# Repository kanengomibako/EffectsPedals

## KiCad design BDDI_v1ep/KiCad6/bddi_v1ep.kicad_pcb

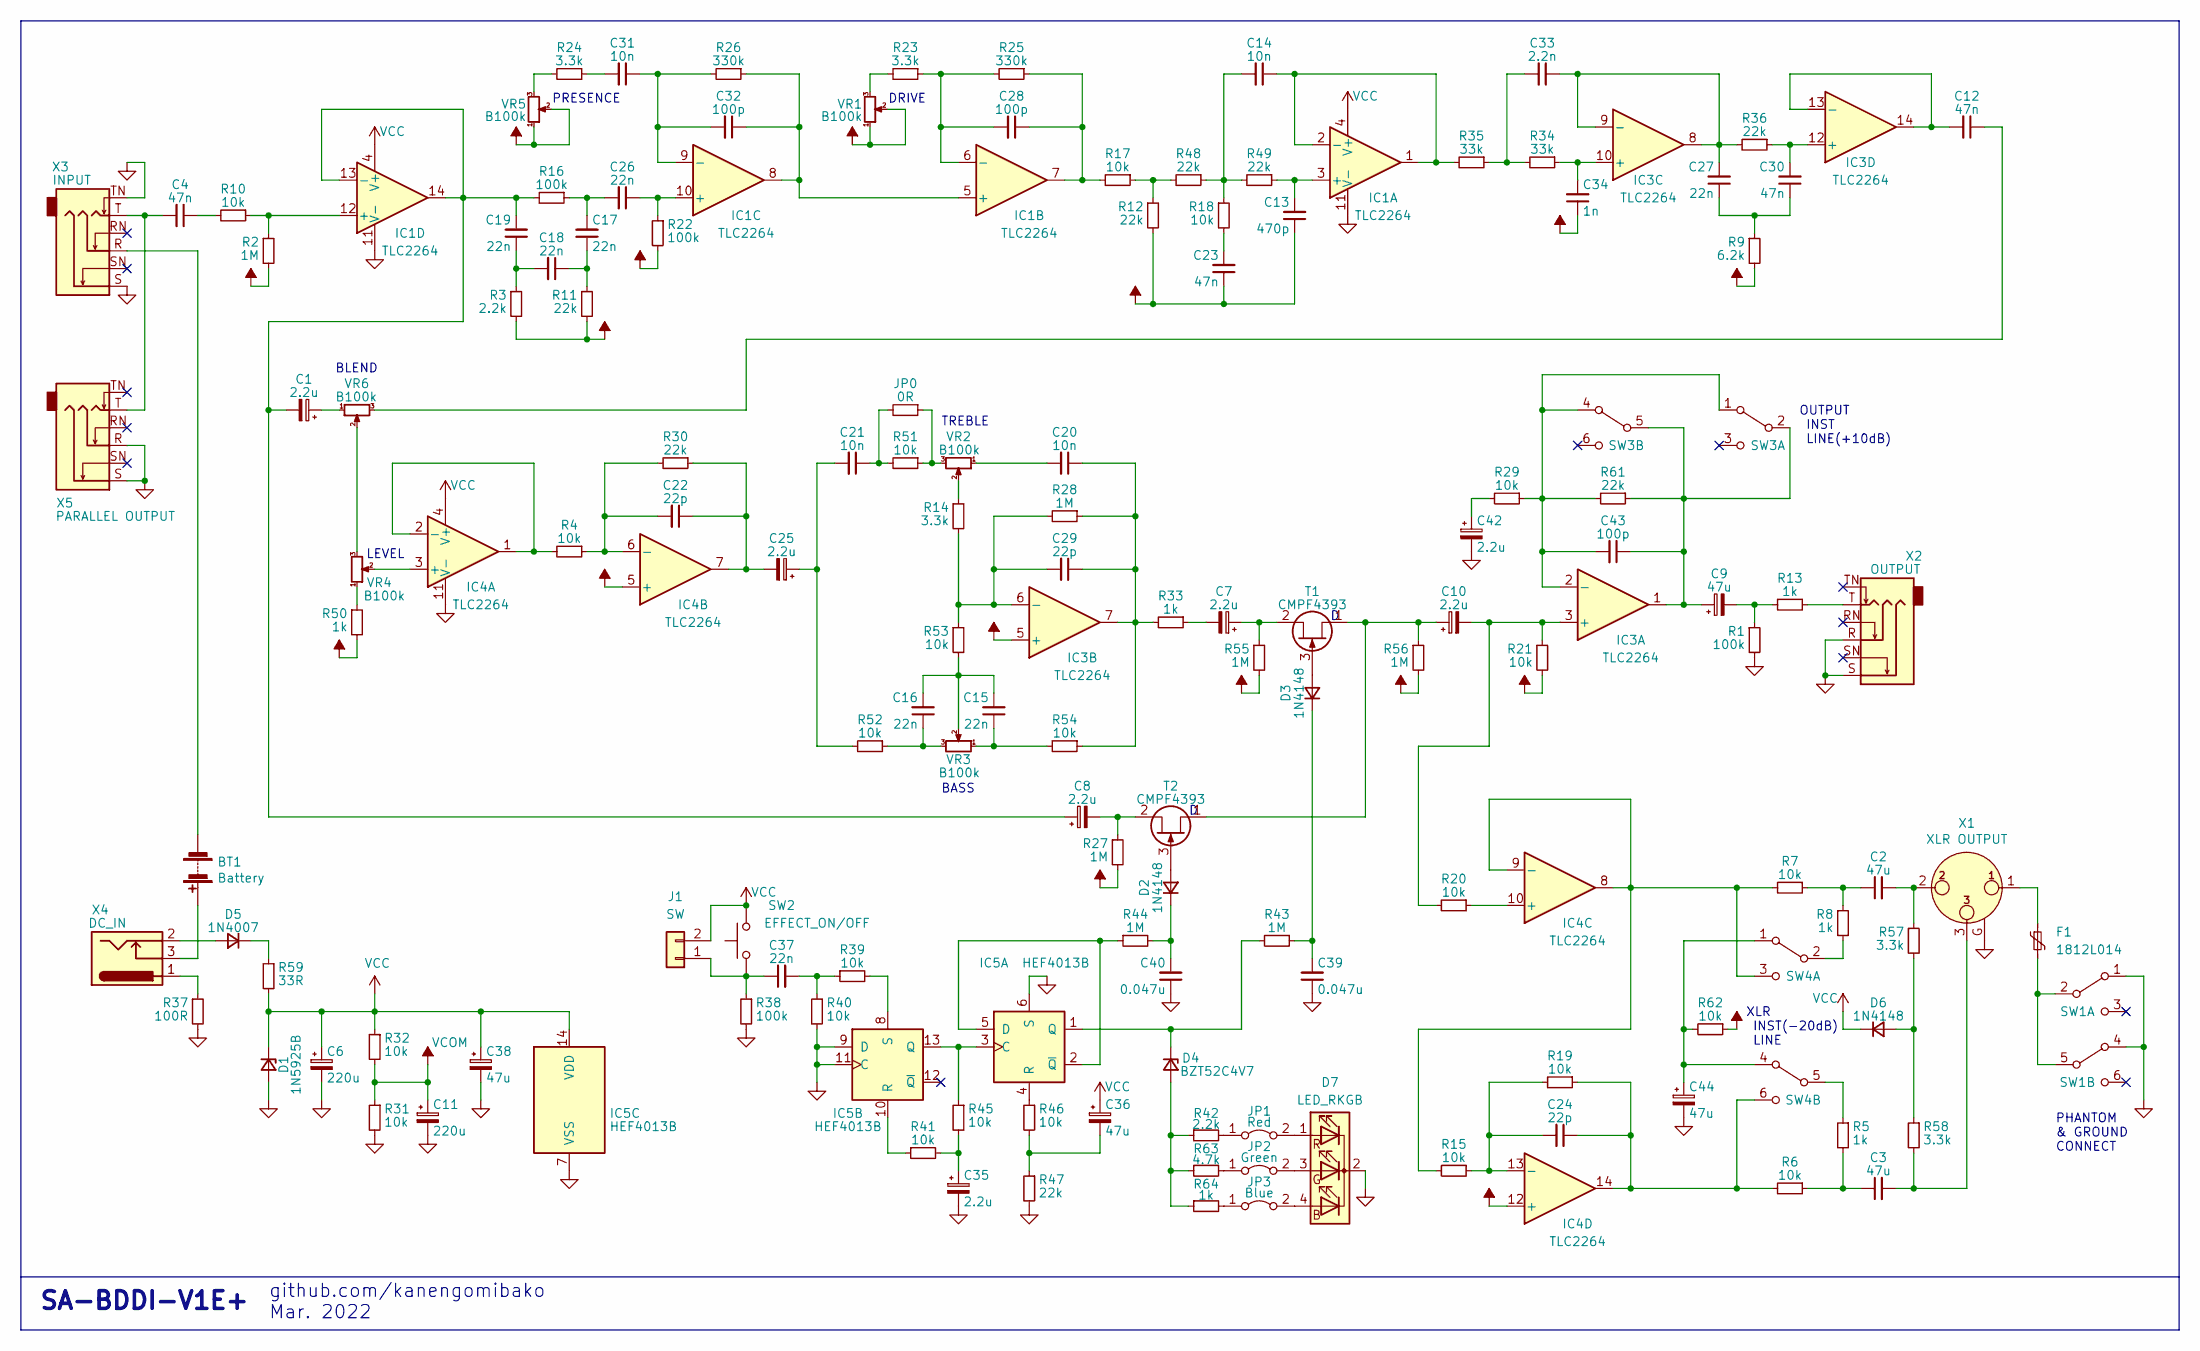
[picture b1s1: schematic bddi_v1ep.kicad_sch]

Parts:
BT1: Battery; PinHeader_1x02_P2.54mm_Vertical
C1, C7, C8, C10, C25, C35, C42: 2.2u; CP_Radial_D5.0mm_P2.00mm
C2, C3: 47u; CP_Radial_D8.0mm_P2.50mm
C4, C12, C23, C30: 47n; C_1210_3225Metric
C6, C11: 220u; CP_Radial_D6.3mm_P2.50mm
C9, C36, C38, C44: 47u; CP_Radial_D5.0mm_P2.00mm
C13: 470p; C_0603_1608Metric_Pad1.08x0.95mm_HandSolder
C14, C20, C21, C31: 10n; C_0603_1608Metric_Pad1.08x0.95mm_HandSolder
C15, C16, C17, C18, C19, C26, C27, C37: 22n; C_0805_2012Metric
C22, C24, C29: 22p; C_0603_1608Metric_Pad1.08x0.95mm_HandSolder
C28, C32, C43: 100p; C_0603_1608Metric_Pad1.08x0.95mm_HandSolder
C33: 2.2n; C_0603_1608Metric_Pad1.08x0.95mm_HandSolder
C34: 1n; C_0603_1608Metric_Pad1.08x0.95mm_HandSolder
C39, C40: 0.047u; C_0603_1608Metric_Pad1.08x0.95mm_HandSolder
D1: 1N5925B; D_DO-41_SOD81_P7.62mm_Horizontal
D2, D3, D6: 1N4148; my_D_GS1010FL
D4: BZT52C4V7; my_D_GS1010FL
D5: 1N4007; D_DO-41_SOD81_P7.62mm_Horizontal
D7: LED_RKGB; LED_D5.0mm-4_RGB
F1: 1812L014; R_1812_4532Metric
IC1, IC3, IC4: TLC2264; TSSOP-14_4.4x5mm_P0.65mm
IC5: HEF4013B; SOIC-14_3.9x8.7mm_P1.27mm
J1: SW; PinHeader_1x02_P2.54mm_Vertical
JP0: 0R; my_SolderJumper-THpad
JP1: Red; my_SolderJumper-THpad
JP2: Green; my_SolderJumper-THpad
JP3: Blue; my_SolderJumper-THpad
R1, R16, R22, R38: 100k; R_0603_1608Metric_Pad0.98x0.95mm_HandSolder
R2, R27, R28, R43, R44, R55, R56: 1M; R_0603_1608Metric_Pad0.98x0.95mm_HandSolder
R3, R42: 2.2k; R_0603_1608Metric_Pad0.98x0.95mm_HandSolder
R4, R6, R7, R10, R15, R17, R18, R19, R20, R21, R29, R31, R32, R39, R40, R41, R45, R46, R51, R52, R53, R54, R62: 10k; R_0603_1608Metric_Pad0.98x0.95mm_HandSolder
R5, R8, R13, R33, R50, R64: 1k; R_0805_2012Metric
R9: 6.2k; R_0603_1608Metric_Pad0.98x0.95mm_HandSolder
R11, R12, R30, R36, R47, R48, R49, R61: 22k; R_0603_1608Metric_Pad0.98x0.95mm_HandSolder
R14, R23, R24, R57, R58: 3.3k; R_0603_1608Metric_Pad0.98x0.95mm_HandSolder
R25, R26: 330k; R_0603_1608Metric_Pad0.98x0.95mm_HandSolder
R34, R35: 33k; R_0603_1608Metric_Pad0.98x0.95mm_HandSolder
R37: 100R; R_Axial_DIN0309_L9.0mm_D3.2mm_P12.70mm_Horizontal
R59: 33R; R_Axial_DIN0516_L15.5mm_D5.0mm_P20.32mm_Horizontal
R63: 4.7k; R_0603_1608Metric_Pad0.98x0.95mm_HandSolder
SW1, SW3, SW4: sw; PinHeader_2x03_P2.54mm_Vertical
SW2: EFFECT_ON/OFF; SW_Cherry_MX_1.00u_PCB
T1, T2: CMPF4393; SOT-23
VR1, VR2, VR3, VR4, VR5, VR6: B100k; my_pot_5mm_widePad
X1: XLR OUTPUT; PinHeader_1x04_P2.54mm_Vertical
X2: OUTPUT; my_Phone_Jack_Daier
X3: INPUT; my_Phone_Jack_Daier
X4: DC_IN; my_DC_Jack
X5: PARALLEL OUTPUT; my_Phone_Jack_Daier

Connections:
GND: C6.2, C11.2, C35.2, C38.2, C39.1, C40.1, C42.2, C44.2, D1.2 (A), D7.2 (K), IC1.11 (V-), IC3.11 (V-), IC4.11 (V-), IC5.6 (S), IC5.7 (VSS), IC5.9 (D), IC5.11 (C), R1.2, R31.2, R37.2, R38.2, R40.2, R47.2, SW1.1 (A), SW1.4 (A), X1.G, X2.R, X2.S, X3.S, X3.TN, X5.R, X5.S
unnamed: BT1.1 (+), X4.3
unnamed: BT1.2 (-), X3.R
unnamed: C1.1, VR6.1
unnamed: C1.2, C8.1, C19.2, IC1.13 (-), IC1.14, R16.2
unnamed: C2.1, R7.1, R8.1
unnamed: C2.2, R57.1, X1.2
unnamed: C3.1, R5.2, R6.1
unnamed: C3.2, R58.2, X1.3
unnamed: C4.1, R10.2
unnamed: C4.2, X3.T, X5.T
unnamed: C7.1, R55.1, T1.2 (S)
unnamed: C7.2, R33.1
unnamed: C8.2, R27.1, T2.2 (S)
unnamed: C9.2, R1.1, R13.2
unnamed: C10.1, R56.1, T1.1 (D), T2.1 (D)
unnamed: C10.2, IC3.3 (+), R20.2, R21.1
unnamed: C12.1, VR6.3
unnamed: C12.2, IC3.13 (-), IC3.14
unnamed: C13.2, IC1.3 (+), R49.1
unnamed: C14.1, IC1.1, IC1.2 (-), R35.2
unnamed: C14.2, R18.1, R48.1, R49.2
unnamed: C15.1, R54.2, VR3.1
unnamed: C15.2, C16.2, R53.2, VR3.2
unnamed: C16.1, R52.1, VR3.3
unnamed: C17.1, C18.1, R11.1
unnamed: C17.2, C26.2, R16.1
unnamed: C18.2, C19.1, R3.1
unnamed: C20.1, C29.1, IC3.7, R28.1, R33.2, R54.1
unnamed: C20.2, VR2.1
unnamed: C21.1, JP0.2, R51.2
unnamed: C21.2, C25.1, R52.2
unnamed: C22.1, C25.2, IC4.7, R30.1
unnamed: C22.2, IC4.6 (-), R4.1, R30.2
unnamed: C23.2, R18.2
unnamed: C24.1, IC4.14, R6.2, R19.1, SW4.6 (C)
unnamed: C24.2, IC4.13 (-), R15.1, R19.2
unnamed: C26.1, IC1.10 (+), R22.1
unnamed: C27.1, C30.1, R9.1
unnamed: C27.2, C33.1, IC3.8, IC3.9 (-), R36.2
unnamed: C28.1, IC1.7, R17.2, R25.1
unnamed: C28.2, IC1.6 (-), R23.1, R25.2
unnamed: C29.2, IC3.6 (-), R14.2, R28.2, R53.1
unnamed: C30.2, IC3.12 (+), R36.1
unnamed: C31.1, C32.2, IC1.9 (-), R26.2
unnamed: C31.2, R24.1
unnamed: C32.1, IC1.5 (+), IC1.8, R26.1
unnamed: C33.2, R34.2, R35.1
unnamed: C34.2, IC3.10 (+), R34.1
unnamed: C35.1, R41.2, R45.2
unnamed: C36.2, R46.2, R47.1
unnamed: C37.1, J1.1, R38.1, SW2.2
unnamed: C37.2, R39.1, R40.1
unnamed: C39.2, D3.1 (K), R43.1
unnamed: C40.2, D2.1 (K), R44.2
unnamed: C42.1, R29.2
unnamed: C9.1, C43.1, IC3.1, R61.1, SW3.2 (B), SW3.5 (B)
unnamed: C43.2, IC3.2 (-), R29.1, R61.2, SW3.1 (A), SW3.4 (A)
unnamed: C44.1, R62.2, SW4.1 (A), SW4.4 (A)
unnamed: D2.2 (A), T2.3 (G)
unnamed: D3.2 (A), T1.3 (G)
unnamed: D4.1 (K), IC5.1 (Q), R43.2
unnamed: D4.2 (A), R42.1, R63.1, R64.1
unnamed: D5.1 (K), R59.1
unnamed: D5.2 (A), X4.2
unnamed: D6.2 (A), R57.2, R58.1
unnamed: D7.1 (RA), JP1.2 (B)
unnamed: D7.3 (GA), JP2.2 (B)
unnamed: D7.4 (BA), JP3.2 (B)
unnamed: F1.1, X1.1
unnamed: F1.2, SW1.2 (B), SW1.5 (B)
unnamed: IC1.12 (+), R2.1, R10.1
unnamed: IC4.1, IC4.2 (-), R4.2
unnamed: IC4.3 (+), VR4.2
unnamed: IC4.8, IC4.9 (-), R7.2, R15.2, SW4.3 (C)
unnamed: IC4.10 (+), R20.1
unnamed: IC5.2 (~Q), IC5.5 (D), R44.1
unnamed: IC5.4 (R), R46.1
unnamed: IC5.8 (S), R39.2
unnamed: IC5.10 (R), R41.1
unnamed: IC5.3 (C), IC5.13 (Q), R45.1
unnamed: JP0.1, R51.1, VR2.3
unnamed: JP1.1 (A), R42.2
unnamed: JP2.1 (A), R63.2
unnamed: JP3.1 (A), R64.2
unnamed: R5.1, SW4.5 (B)
unnamed: R8.2, SW4.2 (B)
unnamed: R12.1, R17.1, R48.2
unnamed: R13.1, X2.T
unnamed: R14.1, VR2.2
unnamed: R23.2, VR1.3
unnamed: R24.2, VR5.3
unnamed: R37.1, X4.1
unnamed: R50.1, VR4.1
unnamed: VR4.3, VR6.2
VCC: C6.1, C36.1, C38.1, D1.1 (K), D6.1 (K), IC1.4 (V+), IC3.4 (V+), IC4.4 (V+), IC5.14 (VDD), J1.2, R32.1, R59.2, SW2.1
VCOM: C11.1, C13.1, C23.1, C34.1, IC3.5 (+), IC4.5 (+), IC4.12 (+), R2.2, R3.2, R9.2, R11.2, R12.2, R21.2, R22.2, R27.2, R31.1, R32.2, R50.2, R55.2, R56.2, R62.1, VR1.1, VR1.2, VR5.1, VR5.2

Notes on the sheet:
github.com/kanengomibako Mar. 2022
PHANTOM & GROUND CONNECT
XLR INST(-20dB) LINE
BLEND
SA-BDDI-V1E+
OUTPUT INST LINE(+10dB)
PRESENCE
DRIVE
LEVEL
BASS
TREBLE

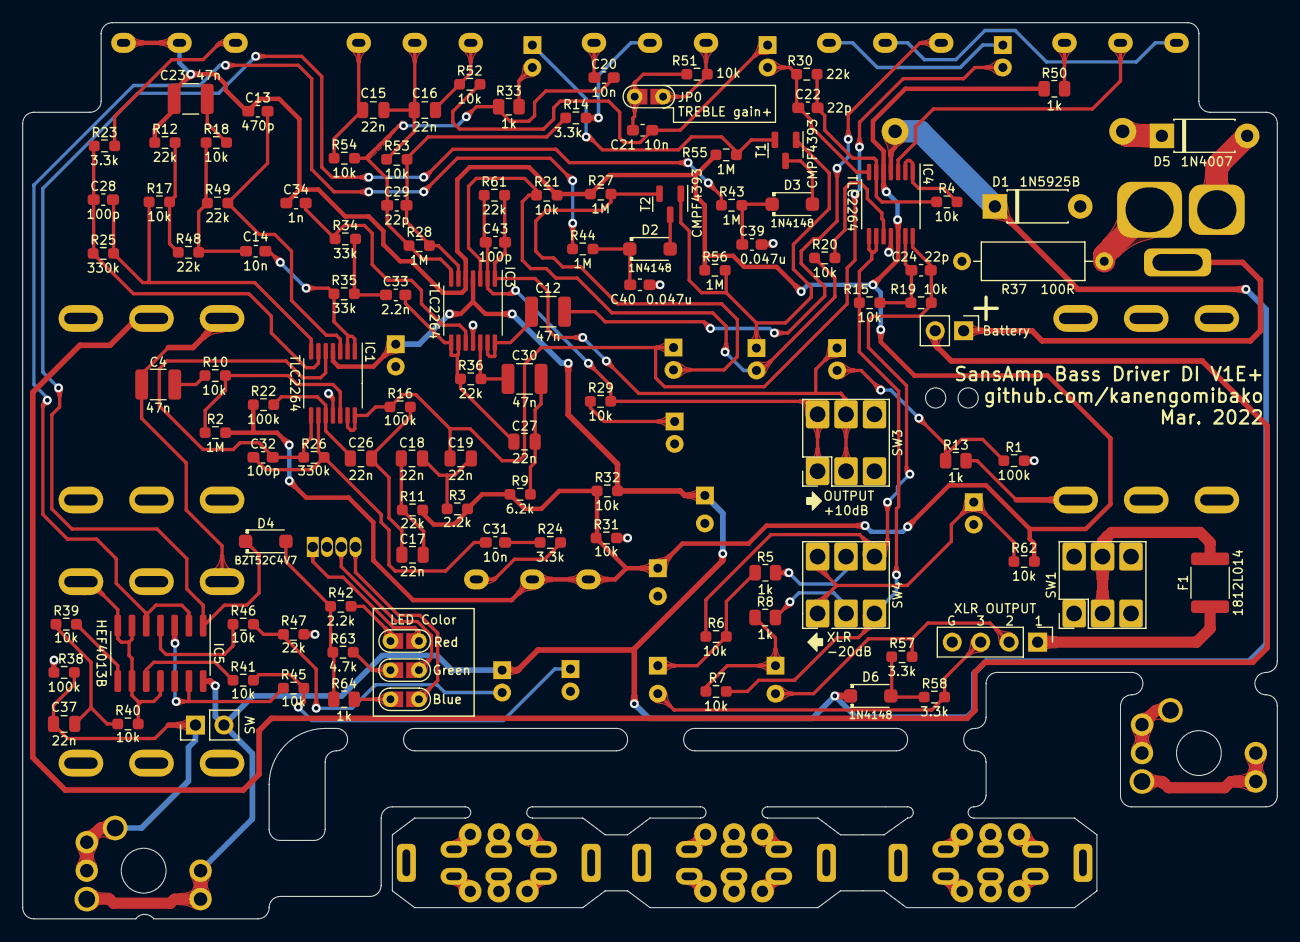
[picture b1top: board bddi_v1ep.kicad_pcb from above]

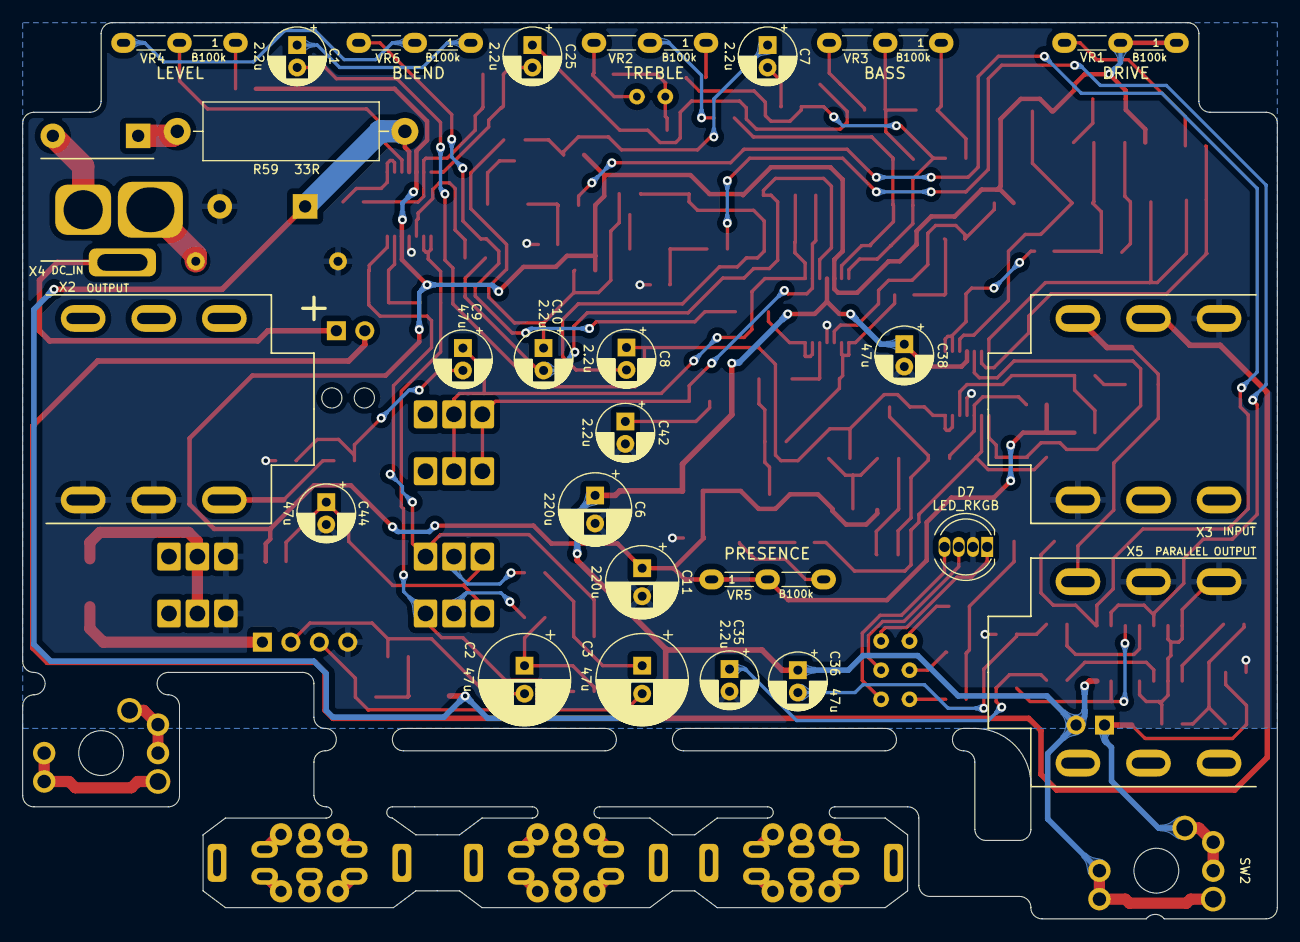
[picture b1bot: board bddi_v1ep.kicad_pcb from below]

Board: 2 copper layers, 112.0 x 80.0 mm, 144 parts (29 on the bottom side), 97 nets.

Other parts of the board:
SW99, SW99#2, SW99#3: sw; PinHeader_2x03_P2.54mm_Vertical
SW99#4: EFFECT_ON/OFF; SW_Cherry_MX_1.00u_PCB

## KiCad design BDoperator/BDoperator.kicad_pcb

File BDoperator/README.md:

BD Operator
[https://kanengomibako.github.io/pages/00362_BDoperator.html](https://kanengomibako.github.io/pages/00362_BDoperator.html)

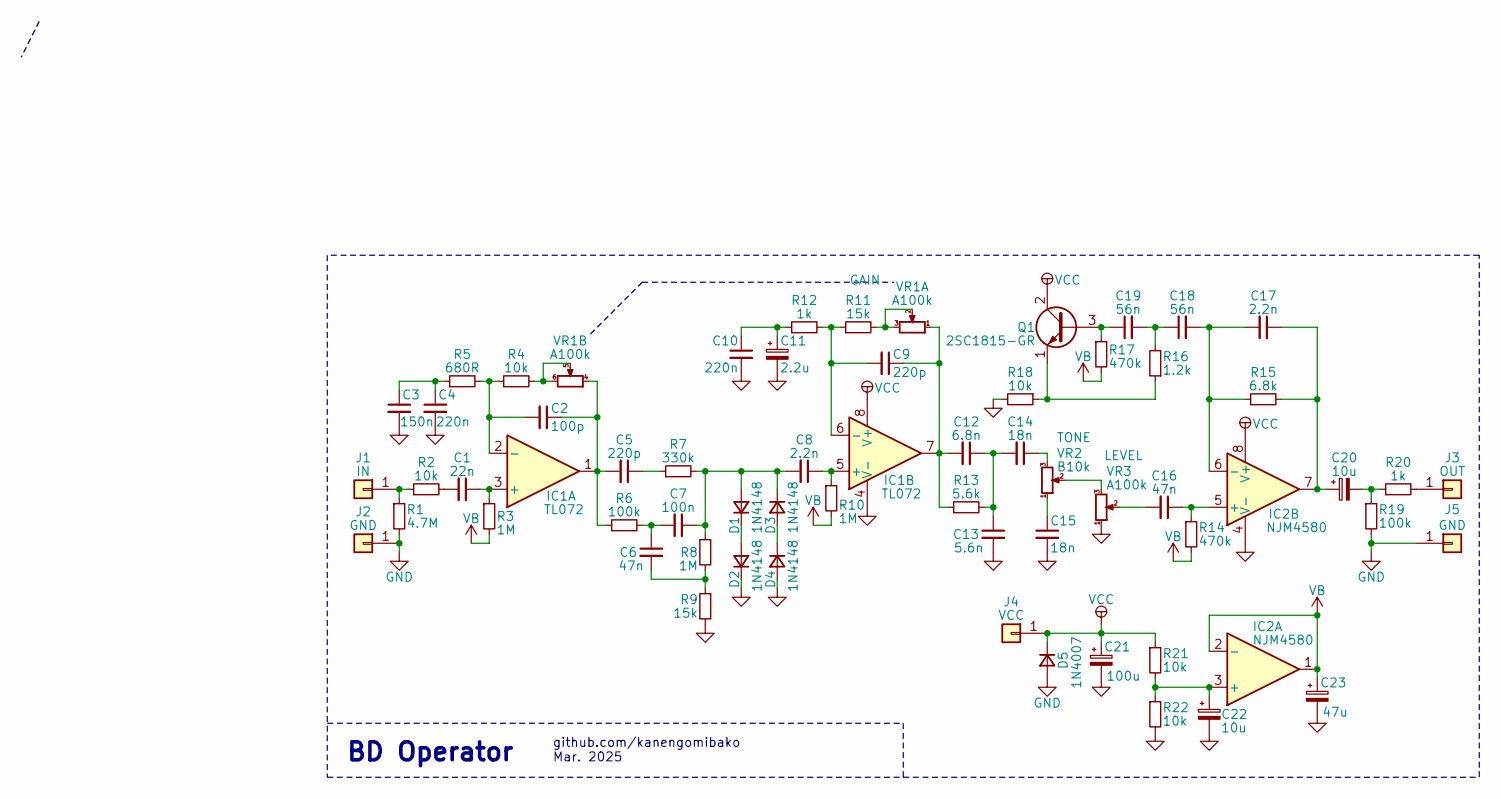
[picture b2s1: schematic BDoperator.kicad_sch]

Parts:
C1: 22n; my_C_Rect1_P5.00mm
C2: 100p; my_C_Rect1_P5.00mm
C3: 150n; my_C_Rect1_P5.00mm
C4, C10: 220n; my_C_Rect1_P5.00mm
C5, C9: 220p; my_C_Rect1_P5.00mm
C6, C16: 47n; my_C_Rect1_P5.00mm
C7: 100n; my_C_Rect1_P5.00mm
C8, C17: 2.2n; my_C_Rect1_P5.00mm
C11: 2.2u; my_C_D5.0mm_P2.50mm
C12: 6.8n; my_C_Rect1_P5.00mm
C13: 5.6n; my_C_Rect1_P5.00mm
C14, C15: 18n; my_C_Rect1_P5.00mm
C18, C19: 56n; my_C_Rect1_P5.00mm
C20, C22: 10u; my_C_D5.0mm_P2.50mm
C21: 100u; my_C_D6.3mm_P2.50mm
C23: 47u; my_C_D5.0mm_P2.50mm
D1, D2, D3, D4: 1N4148; my_D_P7.62mm
D5: 1N4007; my_D_P7.62mm
IC1: TL072; DIP-8_W7.62mm
IC2: NJM4580; DIP-8_W7.62mm
J1: IN; my_WirePad_0-8mmDrill
J2, J5: GND; my_WirePad_0-8mmDrill
J3: OUT; my_WirePad_0-8mmDrill
J4: VCC; my_WirePad_0-8mmDrill
Q1: 2SC1815-GR; TO-92_Inline_Wide
R1: 4.7M; my_R_P7.62mm_Horizontal
R2, R4, R18, R21, R22: 10k; my_R_P7.62mm_Horizontal
R3, R8, R10: 1M; my_R_P7.62mm_Horizontal
R5: 680R; my_R_P7.62mm_Horizontal
R6, R19: 100k; my_R_P7.62mm_Horizontal
R7: 330k; my_R_P7.62mm_Horizontal
R9, R11: 15k; my_R_P7.62mm_Horizontal
R12, R20: 1k; my_R_P7.62mm_Horizontal
R13: 5.6k; my_R_P7.62mm_Horizontal
R14, R17: 470k; my_R_P7.62mm_Horizontal
R15: 6.8k; my_R_P7.62mm_Horizontal
R16: 1.2k; my_R_P7.62mm_Horizontal
VR1: A100k; my_pot_5mm_dual
VR2: B10k; my_pot_5mm
VR3: A100k; my_pot_5mm

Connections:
GND: C3.2, C4.2, C10.2, C11.2, C13.2, C15.2, C21.2, C22.2, C23.2, D2.1 (K), D4.2 (A), D5.2 (A), IC1.4 (V-), IC2.4 (V-), J2.1, J5.1, R1.2, R9.2, R18.2, R19.2, R22.2, VR3.1
unnamed: C1.2, R2.2
unnamed: C2.1, C5.2, IC1.1, R6.1, VR1.4
unnamed: C3.1, C4.1, R5.1
unnamed: C5.1, R7.1
unnamed: C6.1, C7.2, R6.2
unnamed: C6.2, R8.2, R9.1
unnamed: C10.1, C11.1, R12.1
unnamed: C12.1, C13.1, C14.2, R13.2
unnamed: C9.1, C12.2, IC1.7, R13.1, VR1.1
unnamed: C14.1, VR2.3
unnamed: C15.1, VR2.1
unnamed: C16.2, VR3.2
unnamed: C17.1, C20.1, IC2.7, R15.2
unnamed: C18.1, C19.2, R16.2
unnamed: C20.2, R19.1, R20.1
unnamed: C7.1, C8.2, D1.2 (A), D3.1 (K), R7.2, R8.1
unnamed: D1.1 (K), D2.2 (A)
unnamed: D3.2 (A), D4.1 (K)
unnamed: C1.1, IC1.3 (+), R3.1
unnamed: C2.2, IC1.2 (-), R4.1, R5.2
unnamed: C8.1, IC1.5 (+), R10.1
unnamed: C9.2, IC1.6 (-), R11.1, R12.2
unnamed: C22.1, IC2.3 (+), R21.2, R22.1
unnamed: C16.1, IC2.5 (+), R14.1
unnamed: C17.2, C18.2, IC2.6 (-), R15.1
unnamed: J1.1, R1.1, R2.1
unnamed: J3.1, R20.2
unnamed: C19.1, Q1.3 (B), R17.1
unnamed: Q1.1 (E), R16.1, R18.1
unnamed: R4.2, VR1.5, VR1.6
unnamed: R11.2, VR1.2, VR1.3
unnamed: VR2.2, VR3.3
VB: C23.1, IC2.1, IC2.2 (-), R3.2, R10.2, R14.2, R17.2
VCC: C21.1, D5.1 (K), IC1.8 (V+), IC2.8 (V+), J4.1, Q1.2 (C), R21.1

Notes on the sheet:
BD Operator
github.com/kanengomibako Mar. 2025

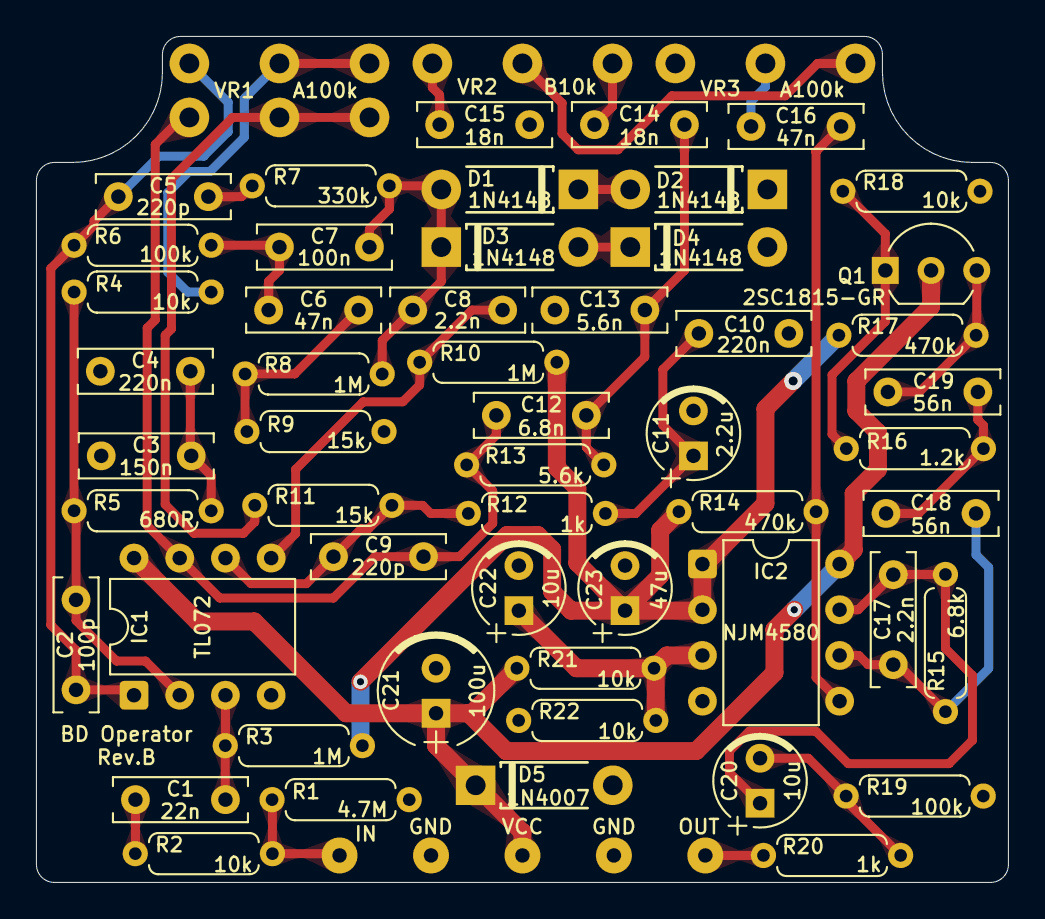
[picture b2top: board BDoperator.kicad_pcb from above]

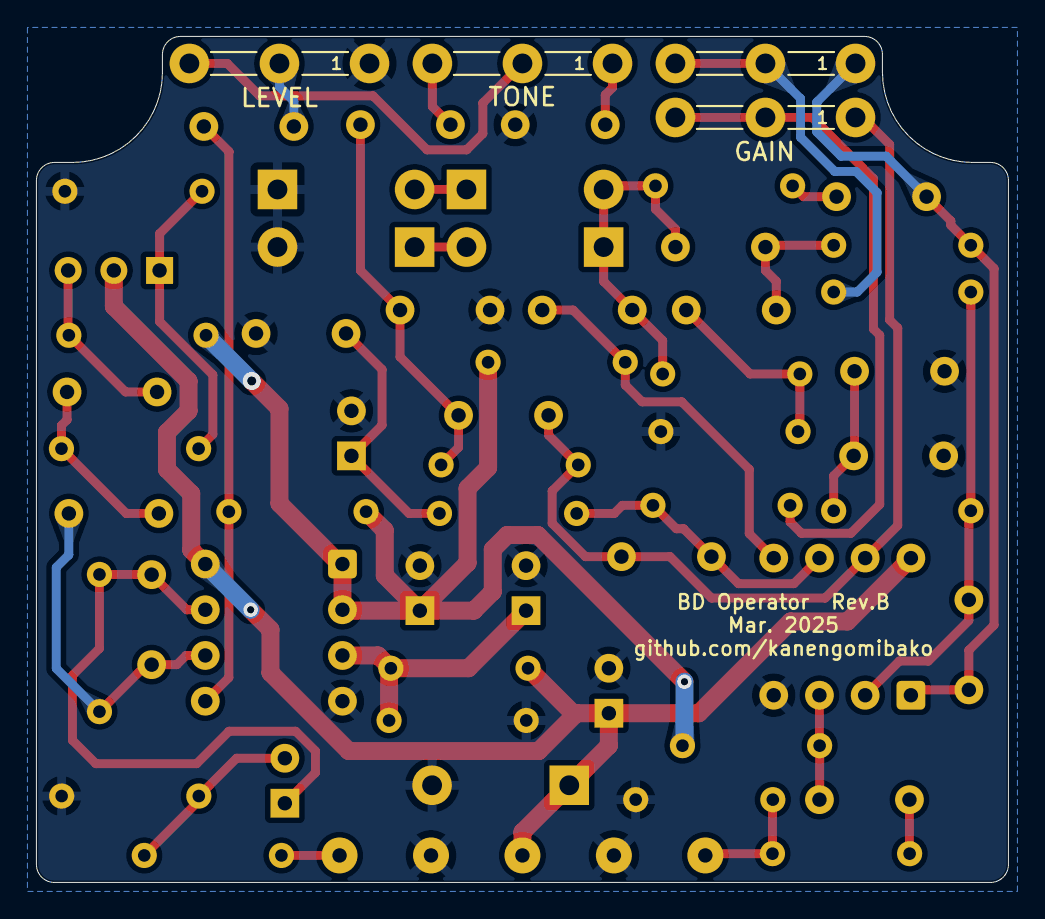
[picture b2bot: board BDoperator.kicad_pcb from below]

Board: 2 copper layers, 54.0 x 47.0 mm, 61 parts (3 on the bottom side), 35 nets.

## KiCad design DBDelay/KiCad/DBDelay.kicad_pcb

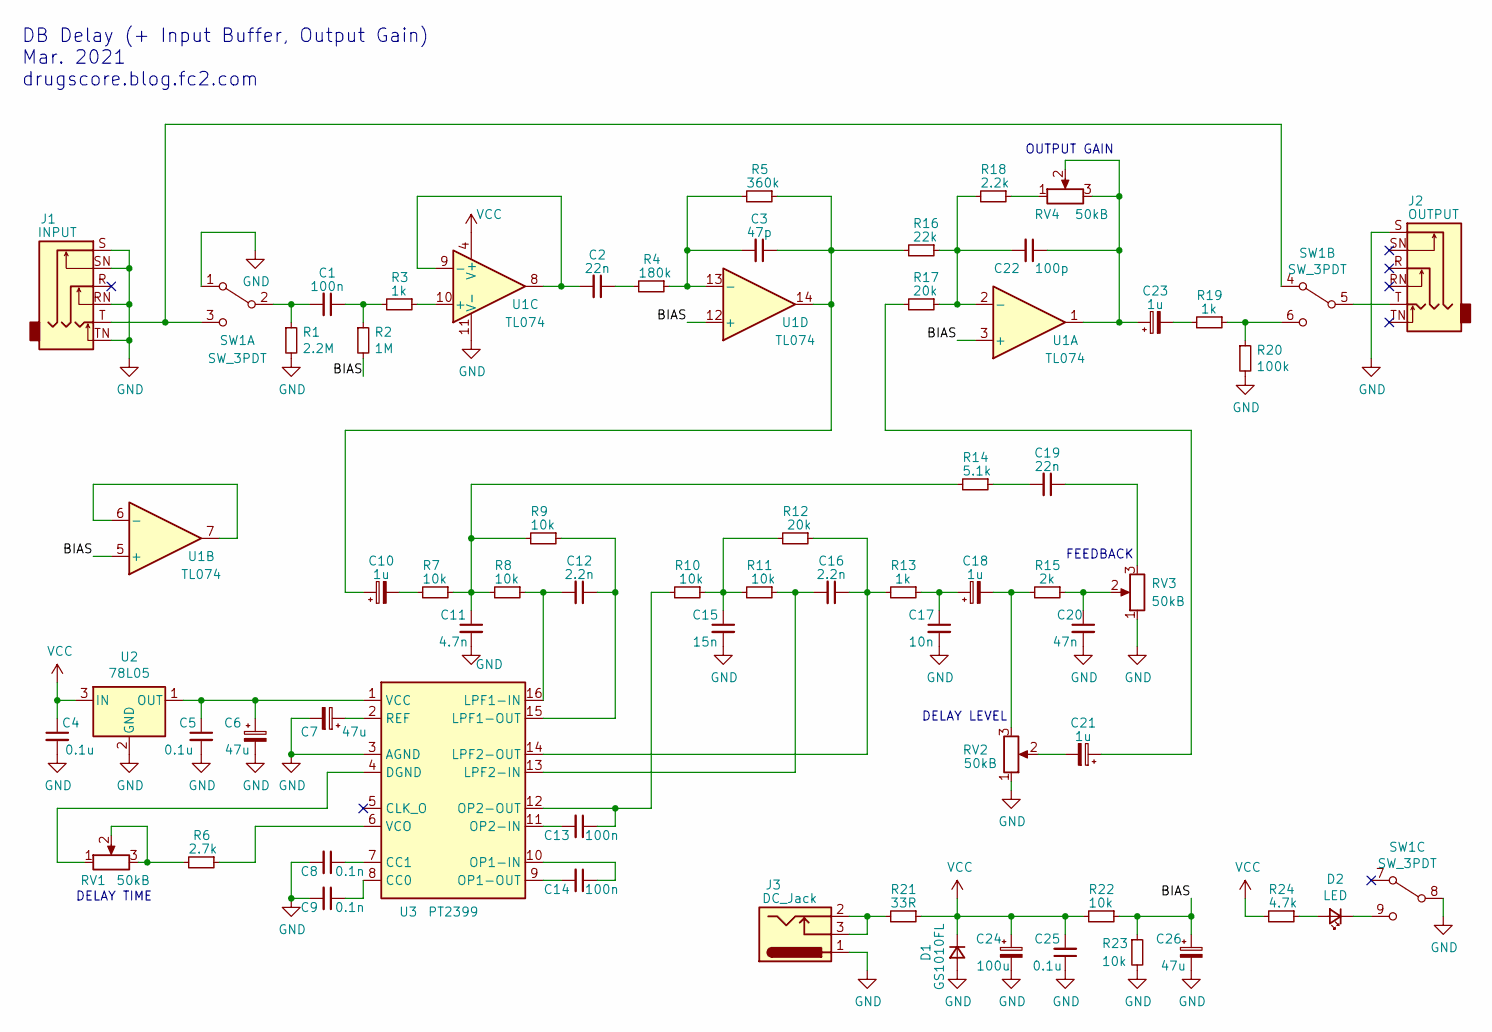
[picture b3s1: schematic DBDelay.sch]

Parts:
C1, C13, C14: 100n; C_1210_3225Metric
C2, C19: 22n; C_0805_2012Metric
C3: 47p; C_0603_1608Metric
C4, C5, C25: 0.1u; C_0603_1608Metric
C6, C7, C26: 47u; CP_Elec_5x5.4
C8, C9: 0.1n; C_0603_1608Metric
C10, C18, C21, C23: 1u; CP_Elec_4x5.4
C11: 4.7n; C_0603_1608Metric
C12, C16: 2.2n; C_0603_1608Metric
C15: 15n; C_0805_2012Metric
C17: 10n; C_0603_1608Metric
C20: 47n; C_1210_3225Metric
C22: 100p; C_0603_1608Metric
C24: 100u; CP_Elec_6.3x5.4
D1: GS1010FL; my_D_GS1010FL
D2: LED; LED_D3.0mm
J1: INPUT; my_Phone_Jack_Daier
J2: OUTPUT; my_Phone_Jack_Daier
J3: DC_Jack; my_DC_Jack
R1: 2.2M; R_0603_1608Metric
R2: 1M; R_0603_1608Metric
R3, R13, R19: 1k; R_0805_2012Metric
R4: 180k; R_0603_1608Metric
R5: 360k; R_0603_1608Metric
R6: 2.7k; R_0603_1608Metric
R7, R8, R9, R10, R11, R22, R23: 10k; R_0603_1608Metric
R12, R17: 20k; R_0603_1608Metric
R14: 5.1k; R_0603_1608Metric
R15: 2k; R_0603_1608Metric
R16: 22k; R_0603_1608Metric
R18: 2.2k; R_0603_1608Metric
R20: 100k; R_0603_1608Metric
R21: 33R; R_0805_2012Metric
R24: 4.7k; R_0603_1608Metric
RV1, RV2, RV3, RV4: 50kB; PinSocket_1x03_P2.54mm_Vertical
SW1: SW_3PDT; my_sw_3pdt
U1: TL074; my_TSSOP-14
U2: 78L05; SOT-89-3
U3: PT2399; DIP-16_W7.62mm

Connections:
/BIAS: C26.1, R2.2, R22.1, R23.1, U1.3 (+), U1.5 (+), U1.12 (+)
GND: C4.2, C5.2, C6.2, C7.2, C8.2, C9.2, C11.2, C15.2, C17.2, C20.2, C24.2, C25.1, C26.2, D1.2 (A), J1.RN, J1.S, J1.SN, J1.TN, J2.S, J3.1, R1.2, R20.2, R23.2, RV2.1, RV3.1, SW1.1 (A), SW1.8 (B), U1.11 (V-), U2.2 (GND), U3.3 (AGND); also elsewhere on the board
unnamed: C1.1, R2.1, R3.2
unnamed: C1.2, R1.1, SW1.2 (B)
unnamed: C2.1, R4.2
unnamed: C2.2, U1.8, U1.9 (-)
unnamed: C3.2, R4.1, R5.2, U1.13 (-)
unnamed: C5.1, C6.1, U2.1 (OUT), U3.1 (VCC)
unnamed: C7.1, U3.2 (REF)
unnamed: C8.1, U3.7 (CC1)
unnamed: C9.1, U3.8 (CC0)
unnamed: C3.1, C10.1, R5.1, R16.2, U1.14
unnamed: C10.2, R7.2
unnamed: C11.1, R7.1, R8.2, R9.2, R14.2
unnamed: C12.1, R9.1, U3.15 (LPF1-OUT)
unnamed: C12.2, R8.1, U3.16 (LPF1-IN)
unnamed: C13.1, R10.2, U3.12 (OP2-OUT)
unnamed: C13.2, U3.11 (OP2-IN)
unnamed: C14.1, U3.10 (OP1-IN)
unnamed: C14.2, U3.9 (OP1-OUT)
unnamed: C15.1, R10.1, R11.2, R12.2
unnamed: C16.1, R12.1, R13.2, U3.14 (LPF2-OUT)
unnamed: C16.2, R11.1, U3.13 (LPF2-IN)
unnamed: C17.1, C18.1, R13.1
unnamed: C18.2, R15.2, RV2.3
unnamed: C19.1, RV3.3
unnamed: C19.2, R14.1
unnamed: C20.1, R15.1, RV3.2
unnamed: C21.1, R17.2
unnamed: C21.2, RV2.2
unnamed: C22.1, C23.1, RV4.2, RV4.3, U1.1
unnamed: C22.2, R16.1, R17.1, R18.2, U1.2 (-)
unnamed: C23.2, R19.2
unnamed: D2.1 (K), SW1.9 (C)
unnamed: D2.2 (A), R24.1
unnamed: J1.T, SW1.3 (C), SW1.4 (A)
unnamed: J2.T, SW1.5 (B)
unnamed: J3.2, J3.3, R21.2
unnamed: R3.1, U1.10 (+)
unnamed: R6.1, U3.6 (VCO)
unnamed: R6.2, RV1.2, RV1.3
unnamed: R18.1, RV4.1
unnamed: R19.1, R20.1, SW1.6 (C)
unnamed: RV1.1, U3.4 (DGND)
unnamed: U1.6 (-), U1.7
VCC: C4.1, C24.1, C25.2, D1.1 (K), R21.1, R22.2, R24.2, U1.4 (V+), U2.3 (IN)

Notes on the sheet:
DELAY TIME
DB Delay (+ Input Buffer, Output Gain) Mar. 2021 drugscore.blog.fc2.com
FEEDBACK
DELAY LEVEL
OUTPUT GAIN

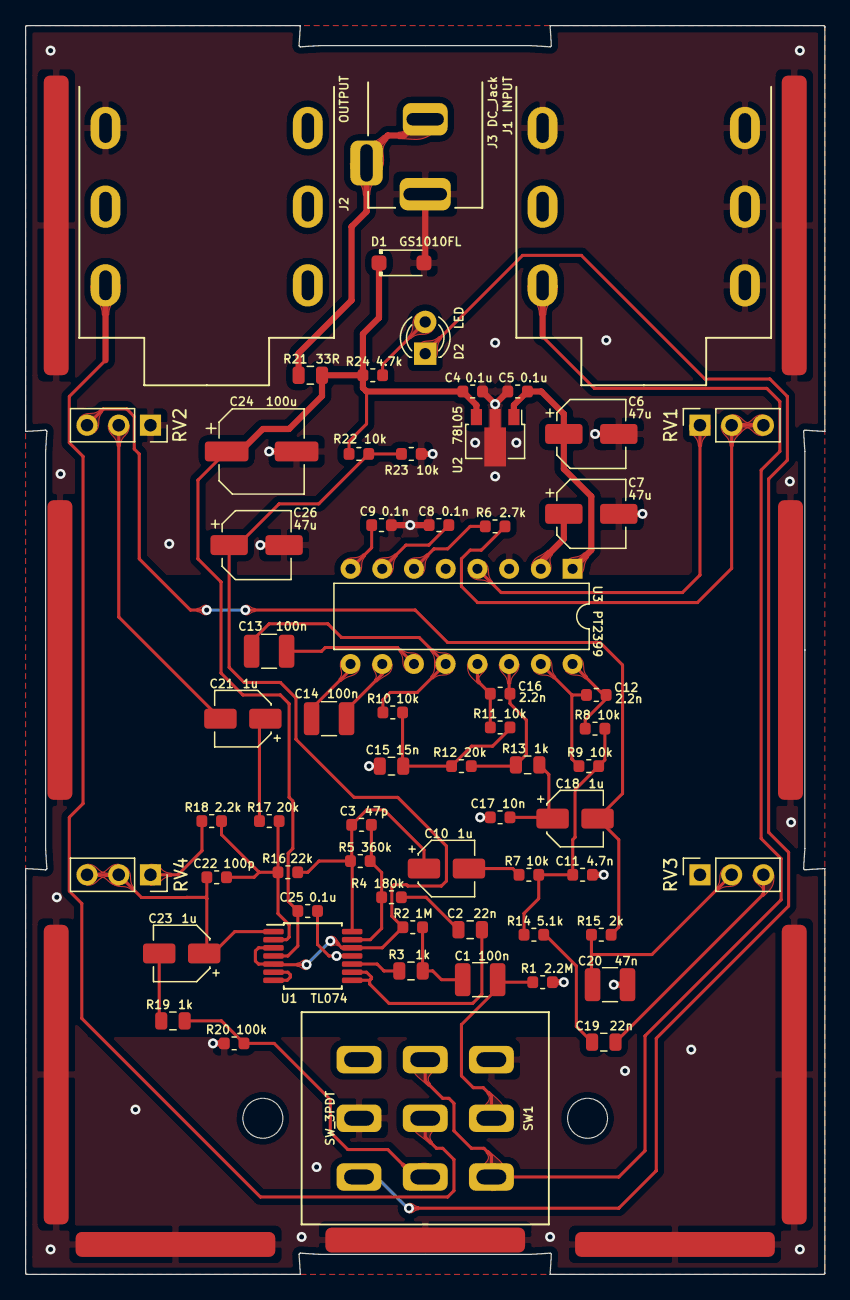
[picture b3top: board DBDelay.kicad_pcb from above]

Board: 2 copper layers, 64.0 x 100.0 mm, 74 parts (0 on the bottom side), 46 nets.

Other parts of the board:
*: *; MountingHole_3.2mm_M3
*#2: *; MountingHole_3.2mm_M3
*#3, *#4, *#5, *#6, *#7, *#8, *#9, *#10, *#11: t; my_TestPoint_2mm

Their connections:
GND: *#3.1, *#4.1, *#5.1, *#6.1, *#7.1, *#8.1, *#9.1, *#10.1, *#11.1; also elsewhere on the board

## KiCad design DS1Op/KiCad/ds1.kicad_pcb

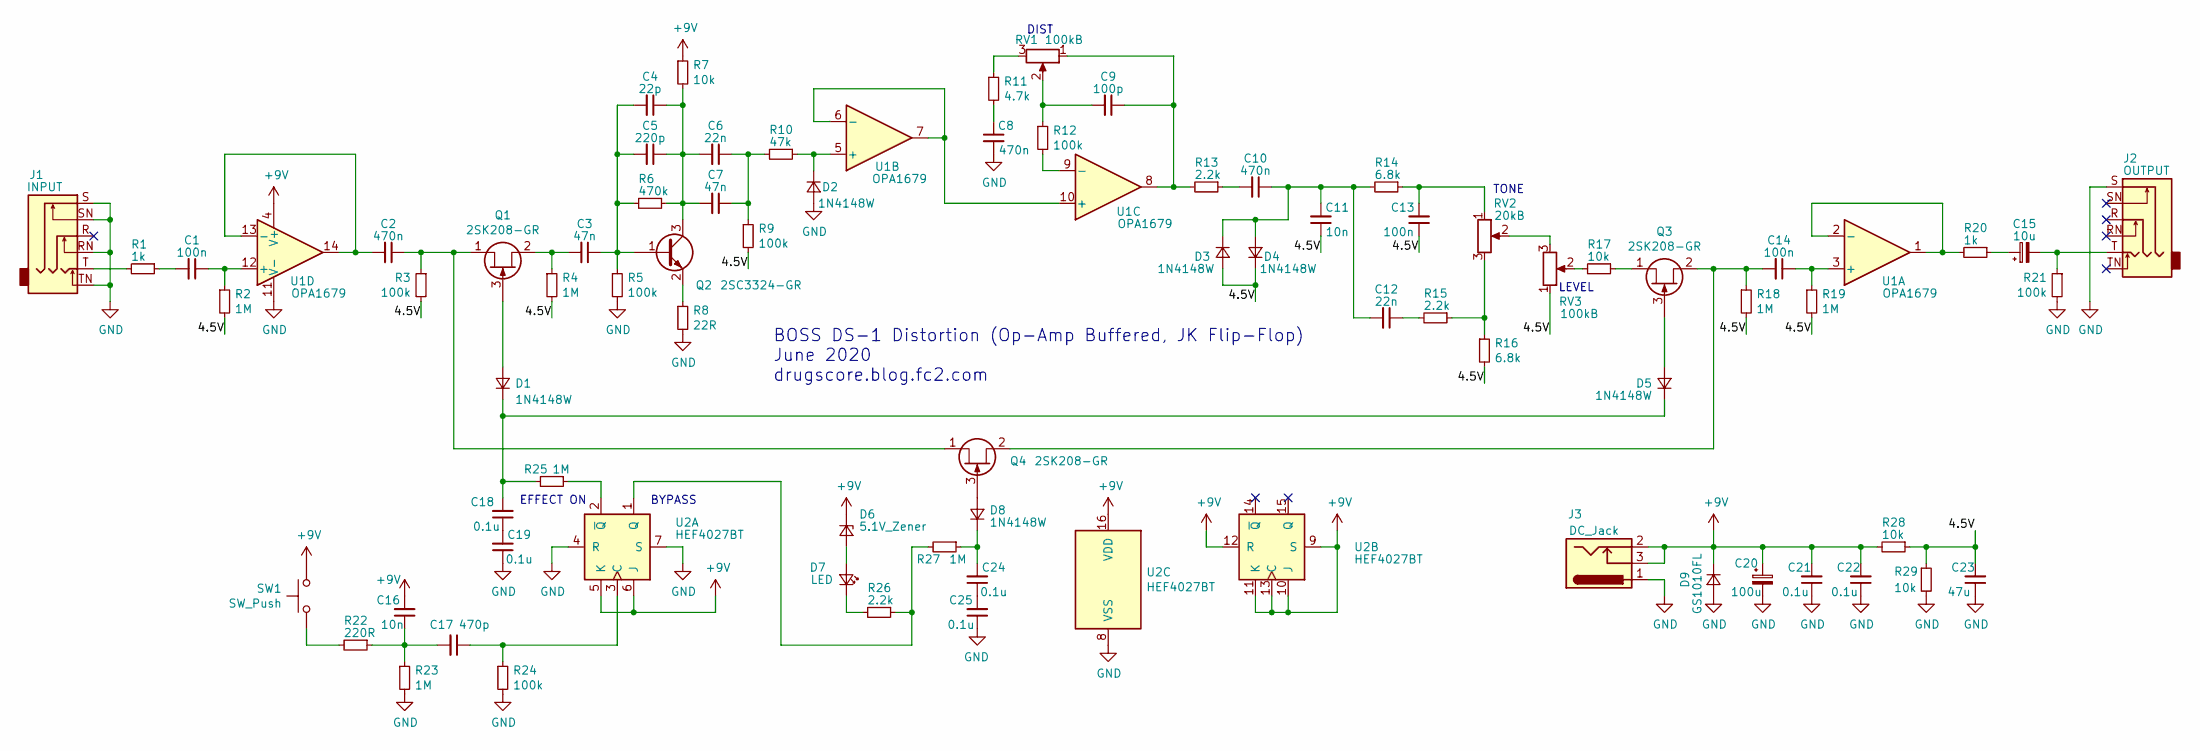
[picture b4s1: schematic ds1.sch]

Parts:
C1, C13, C14: 100n; my_C_3225(1210)_HandSoldering
C2, C8, C10: 470n; my_C_Rect2_P5.00mm
C3, C7: 47n; my_C_3225(1210)_HandSoldering
C4: 22p; my_C_1608(0603)_HandSoldering
C5: 220p; my_C_1608(0603)_HandSoldering
C6, C12: 22n; my_C_2012(0805)_HandSoldering
C9: 100p; my_C_1608(0603)_HandSoldering
C11, C16: 10n; my_C_1608(0603)_HandSoldering
C15: 10u; my_C_Elec_5
C17: 470p; my_C_1608(0603)_HandSoldering
C18, C19, C21, C22, C24, C25: 0.1u; my_C_1608(0603)_HandSoldering
C20: 100u; my_C_Elec_6.3
C23: 47u; my_C_3225(1210)_HandSoldering
D1, D2, D3, D4, D5, D8: 1N4148W; my_D_SOD-123
D6: 5.1V_Zener; my_D_SOD-123
D7: LED; LED_D3.0mm
D9: GS1010FL; my_D_GS1010FL
J1: INPUT; my_Phone_Jack1
J2: OUTPUT; my_Phone_Jack1
J3: DC_Jack; my_DC_Jack
Q1, Q3, Q4: 2SK208-GR; my_SOT-23
Q2: 2SC3324-GR; my_SOT-23
R1, R20: 1k; my_R_2012(0805)_HandSoldering
R2, R4, R18, R19, R23, R25, R27: 1M; my_R_1608(0603)_HandSoldering
R3, R5, R9, R12, R21, R24: 100k; my_R_1608(0603)_HandSoldering
R6: 470k; my_R_1608(0603)_HandSoldering
R7, R17, R28, R29: 10k; my_R_1608(0603)_HandSoldering
R8: 22R; my_R_2012(0805)_HandSoldering
R10: 47k; my_R_1608(0603)_HandSoldering
R11: 4.7k; my_R_1608(0603)_HandSoldering
R13, R15, R26: 2.2k; my_R_1608(0603)_HandSoldering
R14, R16: 6.8k; my_R_1608(0603)_HandSoldering
R22: 220R; my_R_2012(0805)_HandSoldering
RV1, RV3: 100kB; my_Pot_PTV09A-4
RV2: 20kB; my_Pot_PTV09A-4
SW1: SW_Push; my_SKHCBFA010
U1: OPA1679; my_TSSOP-14
U2: HEF4027BT; my_SOIC-16_3.9x9.9mm_Pitch1.27mm

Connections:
+9V: C16.2, C20.1, C21.2, C22.2, D6.1 (K), D9.1 (K), J3.2, J3.3, R7.1, R28.2, SW1.1, U1.4 (V+), U2.5 (K), U2.6 (J), U2.9 (S), U2.10 (J), U2.11 (K), U2.12 (R), U2.13 (C), U2.16 (VDD)
/4.5V: C11.1, C13.1, C23.2, D3.2 (A), D4.1 (K), R2.2, R3.2, R4.2, R9.2, R16.2, R18.2, R19.2, R28.1, R29.1, RV3.1
GND: C8.2, C19.1, C20.2, C21.1, C22.1, C23.1, C25.1, D2.2 (A), D9.2 (A), J1.RN, J1.S, J1.SN, J1.TN, J2.S, J3.1, R5.2, R8.2, R21.2, R23.2, R24.2, R29.2, U1.11 (V-), U2.4 (R), U2.7 (S), U2.8 (VSS)
unnamed: C1.1, R2.1, U1.12 (+)
unnamed: C1.2, R1.1
unnamed: C2.1, Q1.1 (S), Q4.1 (S), R3.1
unnamed: C2.2, U1.13 (-), U1.14
unnamed: C3.1, C4.2, C5.2, Q2.1 (B), R5.1, R6.2
unnamed: C3.2, Q1.2 (D), R4.1
unnamed: C4.1, C5.1, C6.2, C7.2, Q2.3 (C), R6.1, R7.2
unnamed: C6.1, C7.1, R9.1, R10.2
unnamed: C8.1, R11.2
unnamed: C9.1, R13.2, RV1.1, U1.8
unnamed: C9.2, R12.1, RV1.2
unnamed: C10.1, C11.2, C12.2, D3.1 (K), D4.2 (A), R14.2
unnamed: C10.2, R13.1
unnamed: C12.1, R15.2
unnamed: C13.2, R14.1, RV2.1
unnamed: C14.1, R19.1, U1.3 (+)
unnamed: C14.2, Q3.2 (D), Q4.2 (D), R18.1
unnamed: C15.1, R20.1
unnamed: C15.2, J2.T, R21.1
unnamed: C16.1, C17.2, R22.1, R23.1
unnamed: C17.1, R24.1, U2.3 (C)
unnamed: C18.1, C19.2
unnamed: C18.2, D1.1 (K), D5.1 (K), R25.2
unnamed: C24.1, C25.2
unnamed: C24.2, D8.1 (K), R27.1
unnamed: D1.2 (A), Q1.3 (G)
unnamed: D2.1 (K), R10.1, U1.5 (+)
unnamed: D5.2 (A), Q3.3 (G)
unnamed: D6.2 (A), D7.2 (A)
unnamed: D7.1 (K), R26.2
unnamed: D8.2 (A), Q4.3 (G)
unnamed: J1.T, R1.2
unnamed: Q2.2 (E), R8.1
unnamed: Q3.1 (S), R17.1
unnamed: R11.1, RV1.3
unnamed: R12.2, U1.9 (-)
unnamed: R15.1, R16.1, RV2.3
unnamed: R17.2, RV3.2
unnamed: R20.2, U1.1, U1.2 (-)
unnamed: R22.2, SW1.2
unnamed: R25.1, U2.2 (~Q)
unnamed: R26.1, R27.2, U2.1 (Q)
unnamed: RV2.2, RV3.3
unnamed: U1.6 (-), U1.7, U1.10 (+)

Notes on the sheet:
BOSS DS-1 Distortion (Op-Amp Buffered, JK Flip-Flop) June 2020 drugscore.blog.fc2.com
BYPASS
EFFECT ON
TONE
LEVEL
DIST
